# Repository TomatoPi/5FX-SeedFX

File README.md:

# 5FX-SeedFX

## Author

DAGO Esaïe <dago.esaie@protonmail.com>

## Description

Program for DaisySeed used as Guitar Multi-Effect in 5FX-Environment

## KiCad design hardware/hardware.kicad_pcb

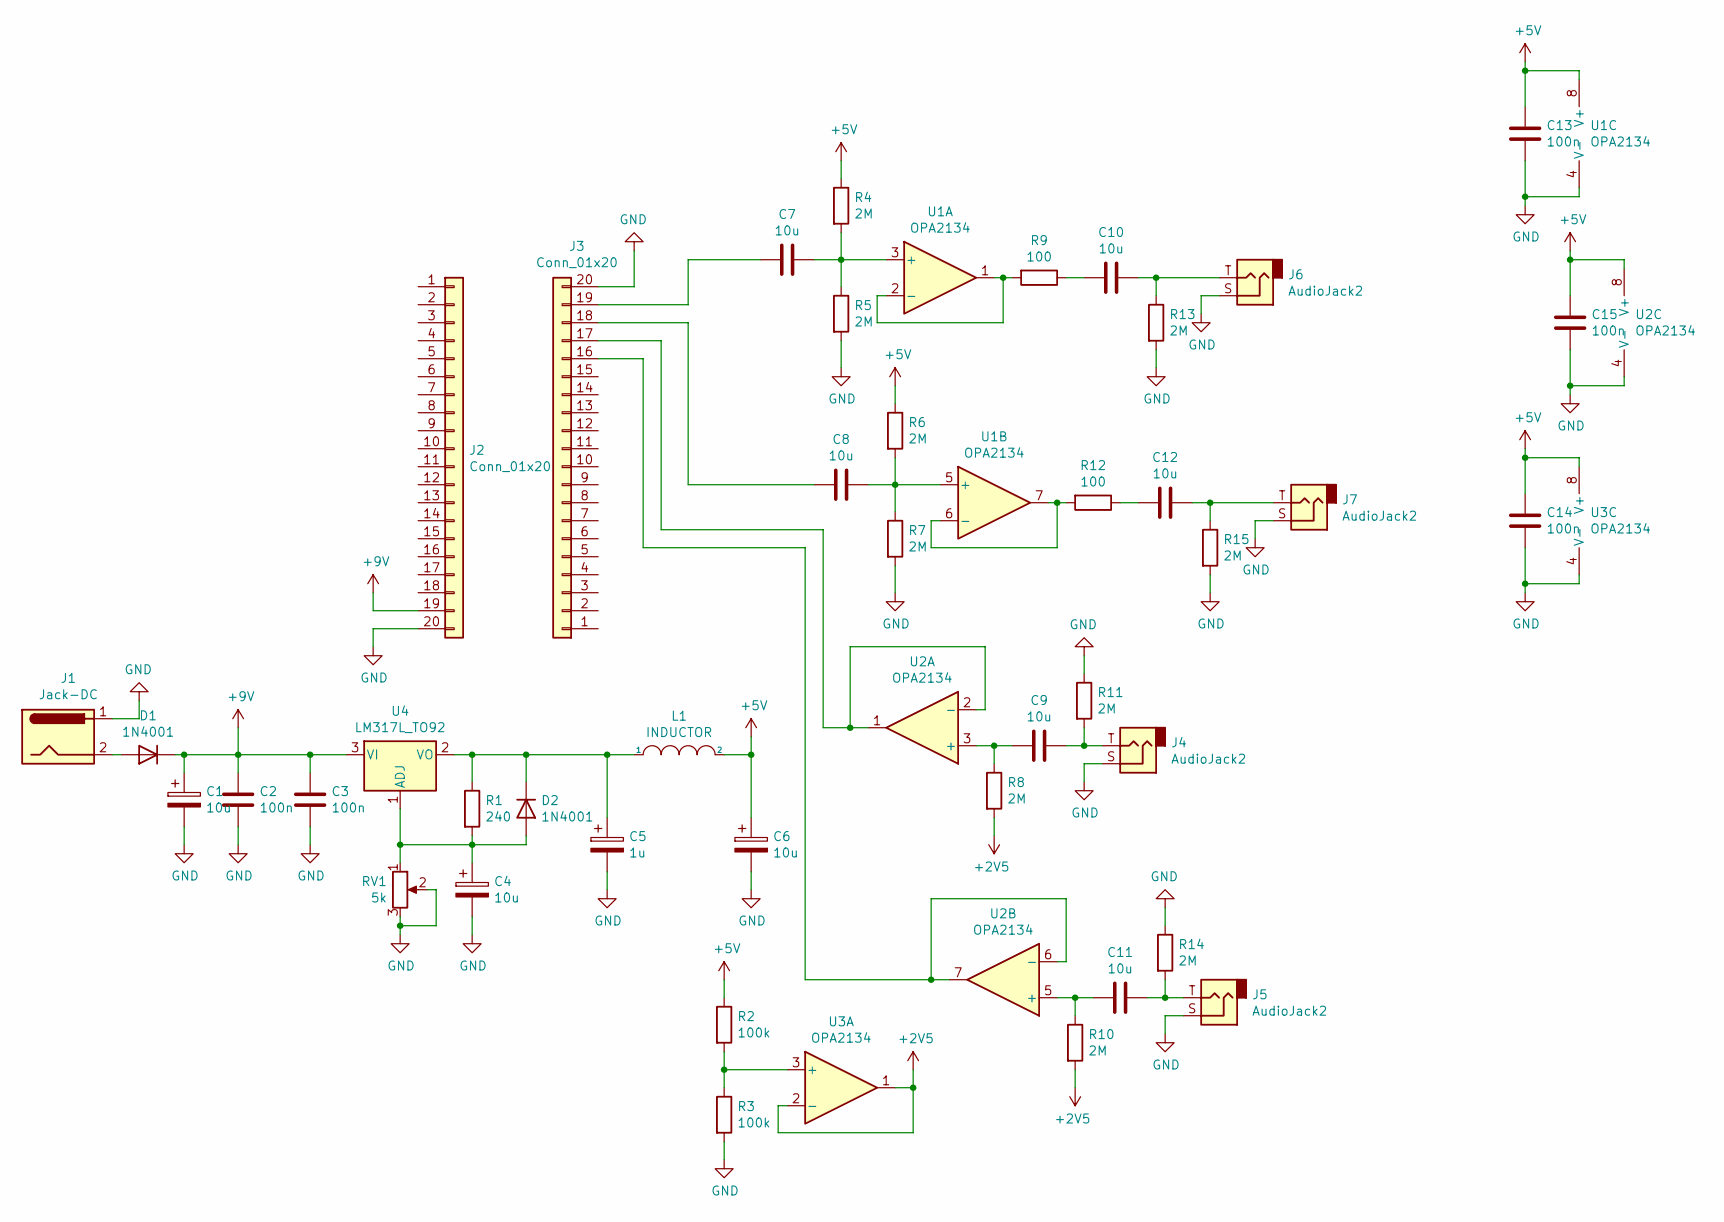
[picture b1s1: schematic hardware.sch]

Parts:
C1, C4, C6, C7, C8, C9, C10, C11, C12: 10u; CP_Radial_D4.0mm_P1.50mm
C2, C3, C13, C14, C15: 100n; CP_Radial_D4.0mm_P1.50mm
C5: 1u; CP_Radial_D4.0mm_P1.50mm
D1, D2: 1N4001; D_DO-41_SOD81_P10.16mm_Horizontal
J1: Jack-DC; PinHeader_1x02_P1.27mm_Horizontal
J2, J3: Conn_01x20; PinHeader_1x20_P1.27mm_Vertical
J4, J5, J6, J7: AudioJack2; PinHeader_1x02_P1.27mm_Vertical
L1: INDUCTOR; L_Radial_D6.0mm_P4.00mm
R1: 240; R_Axial_DIN0204_L3.6mm_D1.6mm_P1.90mm_Vertical
R2, R3: 100k; R_Axial_DIN0204_L3.6mm_D1.6mm_P1.90mm_Vertical
R4, R5, R6, R7, R8, R10, R11, R13, R14, R15: 2M; R_Axial_DIN0204_L3.6mm_D1.6mm_P1.90mm_Vertical
R9, R12: 100; R_Axial_DIN0204_L3.6mm_D1.6mm_P1.90mm_Vertical
RV1: 5k; Potentiometer_Bourns_3006P_Horizontal
U1, U2, U3: OPA2134; DIP-8-16_W7.62mm
U4: LM317L_TO92; TO-92_Inline

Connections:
+2V5: R8.2, R10.2, U3.1, U3.2 (-)
+5V: C6.1, C13.1, C14.1, C15.1, L1.2, R2.1, R4.1, R6.1, U1.8 (V+), U2.8 (V+), U3.8 (V+)
+9V: C1.1, C2.1, C3.1, D1.1 (K), J2.19, U4.3 (VI)
GND: C1.2, C2.2, C3.2, C4.2, C5.2, C6.2, C13.2, C14.2, C15.2, J1.1, J2.20, J3.20, J4.S, J5.S, J6.S, J7.S, R3.2, R5.2, R7.2, R11.1, R13.2, R14.1, R15.2, RV1.2, RV1.3, U1.4 (V-), U2.4 (V-), U3.4 (V-)
unnamed: C4.1, D2.2 (A), R1.2, RV1.1, U4.1 (ADJ)
unnamed: C5.1, D2.1 (K), L1.1, R1.1, U4.2 (VO)
unnamed: C7.1, R4.2, R5.1, U1.3 (+)
unnamed: C7.2, J3.19
unnamed: C8.1, R6.2, R7.1, U1.5 (+)
unnamed: C8.2, J3.18
unnamed: C9.1, J4.T, R11.2
unnamed: C9.2, R8.1, U2.3 (+)
unnamed: C10.1, R9.1
unnamed: C10.2, J6.T, R13.1
unnamed: C11.1, J5.T, R14.2
unnamed: C11.2, R10.1, U2.5 (+)
unnamed: C12.1, R12.1
unnamed: C12.2, J7.T, R15.1
unnamed: D1.2 (A), J1.2
unnamed: J3.16, U2.6 (-), U2.7
unnamed: J3.17, U2.1, U2.2 (-)
unnamed: R2.2, R3.1, U3.3 (+)
unnamed: R9.2, U1.1, U1.2 (-)
unnamed: R12.2, U1.6 (-), U1.7

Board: 2 copper layers, 45 parts (0 on the bottom side), 24 nets, no tracks yet.

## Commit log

2021-02-08 :tada: First commit
2021-02-09 :sparkles: :alembic: Basic Granular Chorus
2021-02-09 Changed window function
2021-02-18 Cleanup + Chorus finish
2021-02-18 Cleanup + Refactored chorus
2021-02-18 Cleanup + reduced static memory usage
2021-02-18 Cleanup + Moved buffer to Utils.hpp
2021-02-18 Refactor
2021-02-18 Added basic looper
2021-02-18 Fix wip
2021-02-19 :ambulance: FIXED
2021-02-19 :art: Cleanup
2021-02-19 :sparkles: Looper
2021-02-19 :ambulance: Final (hopefully) Fix
2021-02-19 :art: Cleanup and refactor
2021-02-19 :sparkles: Added MIDI Parser
2021-02-20 Rx Bug
2021-02-20 :bug: Fixed Midi parsing
2021-02-20 :wrench: Reduced Chorus default gain
2021-02-20 :sparkles: Prototyped persistant saves with QSPI
2021-02-20 :art: Cleanup + prework for complete save and midi integration
2021-02-20 :poop: :building_construction: Moved Chorus params to global fields
2021-02-20 :art: :fix: Massive cleanup + fixed dB litteral
2021-02-21 :art: :sparkles: Cleanup + Basic MIDI controls for the Looper
2021-02-21 :construction: Base for midi param control
2021-02-21 :sparkles: Added basic delay
2021-03-05 Changed Chorus defaults
2021-03-05 Cleanup Pedalboard configuration
2021-03-13 :sparkles: Added Input Gain support
2021-03-13 :sparkles: Added Overdubing
2021-03-14 Improved Looper Control
2021-03-14 :zap: Reduced looper memory usage
2021-03-14 :sparkles: Added Mute function for the Looper
2021-03-22 Removed Global States
2021-06-12 Removed second voice
2021-06-12 Cleaned decibel_gain helper
2021-07-19 new: Added multiply and overdub chg: improved looper memory management bug: oneshot doesn't work
2021-10-01 Improving serial protocol
2021-10-09 serialisation utilities prototype
2021-10-23 some random shit, trying to add modular graph
2021-10-23 Added dynamic allocator utility
2021-10-23 added pool allocator
2021-10-24 basis of dynamic connection managment
2021-10-24 Added logical connection managment, need testing
2021-11-25 small improvements
2021-11-29 small fixes, added detailed error mecanism
2021-11-29 graph computation seems to work well
2021-11-30 fixed buffer's sample allocation
2021-11-30 small refactoring
2021-12-07 finished basis of jack system
2021-12-07 Transformed heterogenous allocator to std compliant version
2021-12-07 prepare hardware tests
